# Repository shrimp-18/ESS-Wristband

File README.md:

# ESSync Wristband

A gesture-controlled referee wristband that automates match timing in Taekwondo. Using an accelerometer and microcontroller, it detects the referee’s calibrated start and stop gestures and wirelessly updates the central timer visible to everyone. This system removes manual jury control, ensuring accurate, fair, and transparent timekeeping.

---

## How it works

- Referee wants to stop the match.
- They make a swift hand movement used traditionally in Taekwondo.
- Players see this hand movement and stop.
- ESSync senses this swift hand movement and sends a signal to the central timer to stop.
- The central timer stops, and so do all the other sensors.
- Similar process repeats when the referee wants to restart the match.

<br>

---

## Why is ESSync Needed?

In Taekwondo matches, round timing is controlled by officials sitting at the jury table rather than by the referee overseeing the bout. This separation often leads to inconsistencies in the start and stop of the timer, whether due to human delay, miscommunication, or, in some cases, bias.
As a result, athletes can be unfairly advantaged or disadvantaged by inaccurate match durations, compromising the fairness and integrity of the competition.
There is a critical need for a referee-operated, automated, and transparent timing system that ensures real-time synchronisation and impartial timekeeping.

---

## So What's the solution?!

- A gesture-controlled wristband worn by referees to automate match timing.
- Uses an accelerometer and microcontroller to detect specific referee gestures.
- The downward "stop" motion of the hand instantly triggers the central arena timer wirelessly.
- Calibrated for each referee to prevent false detections and ensure precision.
- Removes jury dependency, ensuring fair, transparent, and real-time timekeeping.
- The timer part of Taekwondo matches isn’t automated yet and really needs a cheap and effective solution.
- Wristbands are easy to make and reliable.

---

## Components and their uses

| Component | Purpose |
|-----------|---------|
| ESP32-C3 DevKitM-1 | Main MCU, the "brain" of the wristband |
| MPU6050 | Detects referee hand gestures |
| 1.3" 240×240 SPI Display | Displays timer and status |
| MT3608 | Boost converter |
| TP4056 | LiPo battery charger |

---

## Top PCB

---

## Bottom PCB

The project is made with two PCBs. The upper PCB holds the display, while the bottom PCB contains the MCU and all other components. This approach keeps the wristband compact without making it too wide. In future revisions, I plan to make it even smaller. The Case closes shut using the magnets present on the bottom part of the case and the lid of the case. The PCBs are snug in the case. The bottom PCB is also mounted to the bottom case by simply fitting the PCB's holes over the protruding cylindrical parts on the inner base of the case.

---

## Fusion Files

https://a360.co/4gCFWl9

---

## How to Build

## 1. Manufacture the PCBs
Fabricate both the **Top PCB** and **Bottom PCB** using the KiCad Files provided.

---

## 2. Prepare the Components

Purchase all required components listed in the **Bill of Materials (BOM)**.

---

## 3. Solder the Bottom PCB

Assemble the Bottom PCB first.
Solder All components and connectors to the bottom PCB according to the KiCad files given, and attach their respective components.

Refer to the schematic for the correct connector orientation and pin mapping.

---

## 4. Assemble the Top PCB

1. Solder the female headers for the ESP32 connector(on the bottom side).
2. Solder the male headers for the SPI Screen(on the top side).
3. Connect the SPI Screen.

---

## 5. Join the Two PCBs

Carefully align the connector pins and stack the 2 PCBs.

---

## 6. Upload the Firmware

1. Connect the ESP32-C3 to your computer using a USB cable.
2. Open the firmware in the Arduino IDE.
3. Select **ESP32-C3 Dev Module** as the target board.
4. Choose the correct serial port.
5. Compile and upload the firmware.

## 7. Assemble the Enclosure

3D-print the enclosure using the CAD files.

Install the assembled electronics inside the case.
No screws are required to mount as the pcb is snug in the case.
Glue Magnets to the base and lid of the case so that it can remain closed.

---

## 8. Attach a Wrist Strap

The wrist strap is **not** 3D printed </3
It's a DIY thing you need to do with a leather sheet.
Please add a strap to the bottom case through the space given underneath (I will be updating this with a better option in the future).

---

## 9. Power On

If assembled correctly, ESSync should be working! YAY!

---
## How to Use

You'll need to calibrate your hand gestures with the watch so it can record those values and stop/start the timer the next time you use it.

## Bill of Materials

| S.No. | Reference | Value | Product | Notes | Qty | Cost | Link |
|------:|-----------|-------|---------|-------|----:|-----:|------|
| 1 | SPI_SCREEN1 | Conn_01x07 | Connector Pin Socket P2.54mm Vertical 1×7 | Top PCB (Display Connector) | 1 | $0.09 | https://robocraze.com/products/40x1-female-berg-strip |
| 2 | — | — | 1.3" 240×240 SPI Display | External Module | 1 | $9.50 | https://www.waveshare.com/1.3inch-lcd-module.htm |
| 3 | U3 | ESP32-C3-DevKitM-1 | ESP32-C3 DevKitM-1 | Bottom PCB | 1 | $10.11 | https://www.electropi.in/espressif-esp32-c3-devkitm-1-n4x-development-board |
| 4 | J1, J2 | Conn_01x15 | 1×15 Female Pin Socket | Bottom of Top PCB | 2 | $0.09 | https://robocraze.com/products/40x1-female-berg-strip |
| 5 | J7, J8, J9, J10 | Conn_01x01 | 1×01 Pin Header | MT3608 Connection | 4 | $0.06 | https://robocraze.com/products/40x1-pin-2-54mm-pitch-male-berg-strip |
| 6 | — | — | MT3608 Boost Module | External Module | 1 | $0.47 | https://www.flyrobo.in/mt3608-2a-dc-dc-boost-ultra-power-module |
| 7 | MPU6050 | Conn_01x08 | 1×08 Pin Header | MPU6050 Connector | 1 | $0.06 | https://robocraze.com/products/40x1-pin-2-54mm-pitch-male-berg-strip |
| 8 | — | — | MPU6050 Module | External Module | 1 | $1.63 | https://robocraze.com/products/mpu-6050-triple-axis-accelerometer-gyroscope-module |
| 9 | J5, J6, J11, J12 | Conn_01x01 | 1×01 Pin Header | TP4056 Connection | 4 | $0.06 | https://robocraze.com/products/40x1-pin-2-54mm-pitch-male-berg-strip |
| 10 | — | — | TP4056 Charging Module | External Module | 1 | $0.17 | https://quartzcomponents.com/products/tp4056-battery-charging-module |
| 11 | S1 | Tactile Button, 160gf | TS-1088-AR02016 | ESP ON Button | 1 | $0.06 | https://jlcpcb.com/partdetail/XUNPU-TS_1088AR02016/C720477 |
| 12 | SW1 | SW_Slide_DPDT | PCM12 Slide Switch | Power Switch | 1 | $1.20 | https://www.digikey.in/en/products/detail/c-k/PCM12SMTR/1640112 |
| 13 | Battery1 | Conn_01x02 | JST Battery Connector | Battery Connector | 1 | $0.05 | https://robu.in/product/b2b-xh-alfsn-jst-1x2p-2p-xh-tin-2-25%E2%84%8385%E2%84%83-3a-1-2-5mm-brass-direct-insert-pluginp2-5mm-wire-to-board-connector-rohs/ |
| 14 | — | — | 3.7V LiPo Battery | External Module | 1 | $1.69 | https://robocraze.com/products/450mah-3-7v-lipo-rechargeable-battery |
| 15 | C1 | 0.1µF | 0603 Capacitor | Decoupling Capacitor | 1 | $0.04 | https://robu.in/product/0603b104j500nt-fh-50v-100nf-x7r%C2%B15-0603-multilayer-ceramic-capacitors-mlcc-smd-smt-rohs/ |
| 16 | — | — | PCB Fabrication | Two Custom PCBs | 2 | $2.00 | https://cart.jlcpcb.com/quote |
| 17 | — | — | 3D Printed Case | External | 1 | $4.00 | https://zbotic.in/product/online-3d-printing-service |
| 18 | — | — | Leather Strap | External | 1 | $0.40 | https://www.desertcart.in/products/425174482-genuine-leather-strip-1-2-inch-wide-72-inches-long |
| 19 | — | — | Magnets | Externsl | 1 | $0.40 | https://www.prayogindia.in/product/neodymium-magnet-3mm-x-1mm-n35-super-strong-magnets/ |

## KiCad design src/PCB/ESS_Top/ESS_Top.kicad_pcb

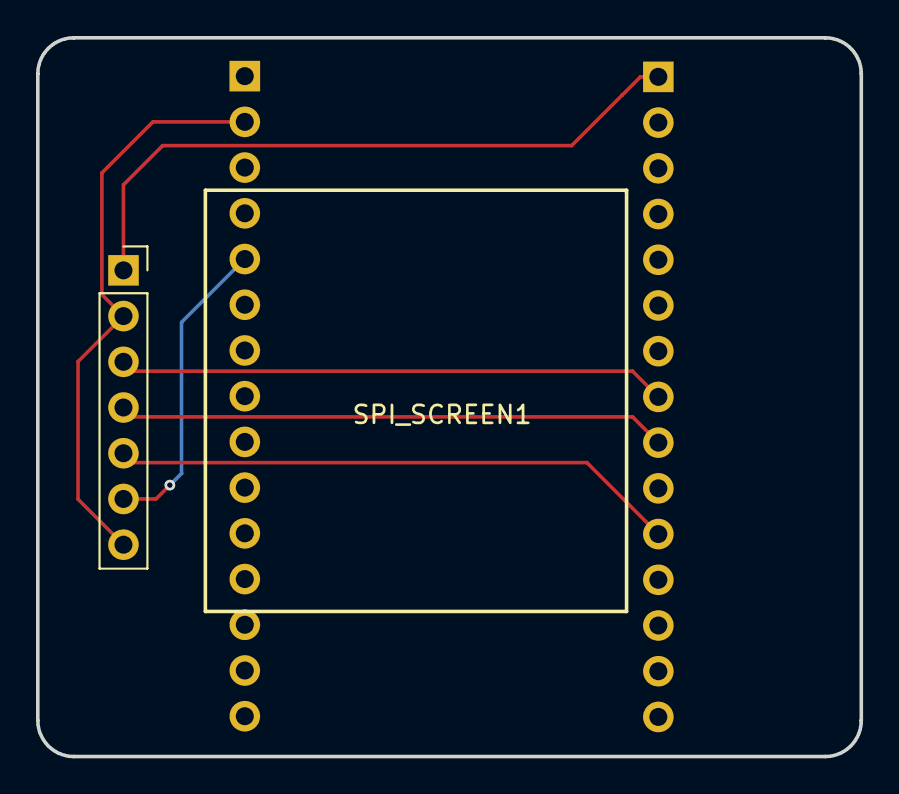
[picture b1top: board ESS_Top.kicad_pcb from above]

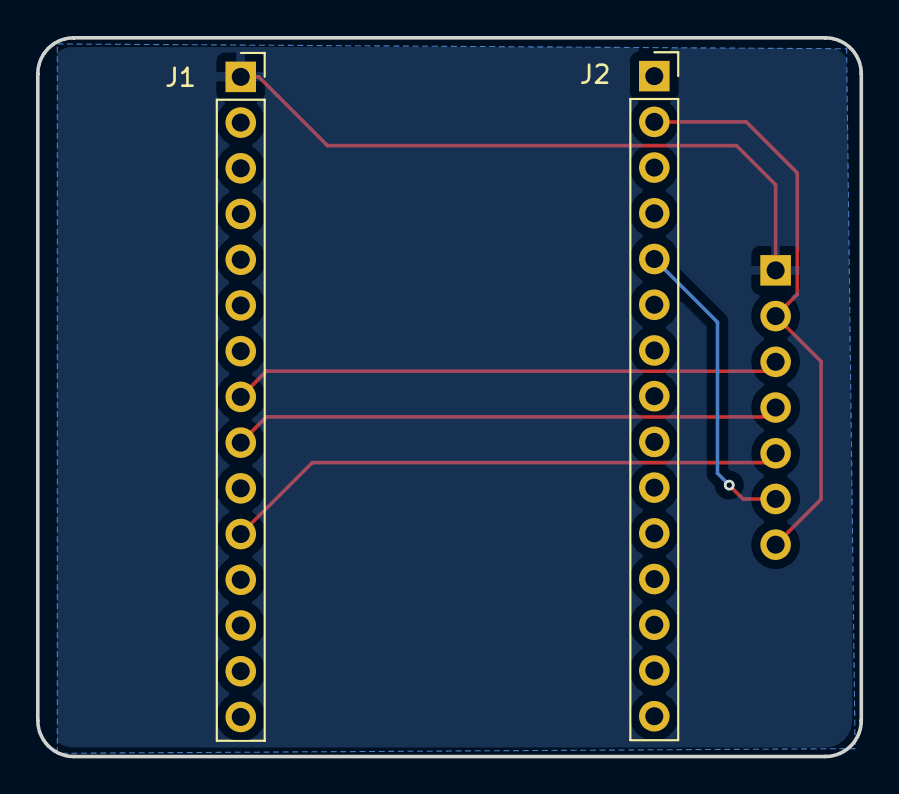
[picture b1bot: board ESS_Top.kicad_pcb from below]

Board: 2 copper layers, 45.7 x 39.9 mm, 3 parts (2 on the bottom side), 6 nets.

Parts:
J1, J2: Conn_01x15; PinSocket_1x15_P2.54mm_Vertical
SPI_SCREEN1: Conn_01x07; PinSocket_1x07_P2.54mm_Vertical

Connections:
+3.3V: J2.2 (3V3), SPI_SCREEN1.2, SPI_SCREEN1.7
/DC: J2.5 (GPIO3), SPI_SCREEN1.6
/RES: J1.11 (GPIO4), SPI_SCREEN1.5
/SCL_SPI: J1.8 (GPIO7), SPI_SCREEN1.3
/SDA_SPI: J1.9 (GPIO6), SPI_SCREEN1.4
GND: J1.1 (GND), SPI_SCREEN1.1

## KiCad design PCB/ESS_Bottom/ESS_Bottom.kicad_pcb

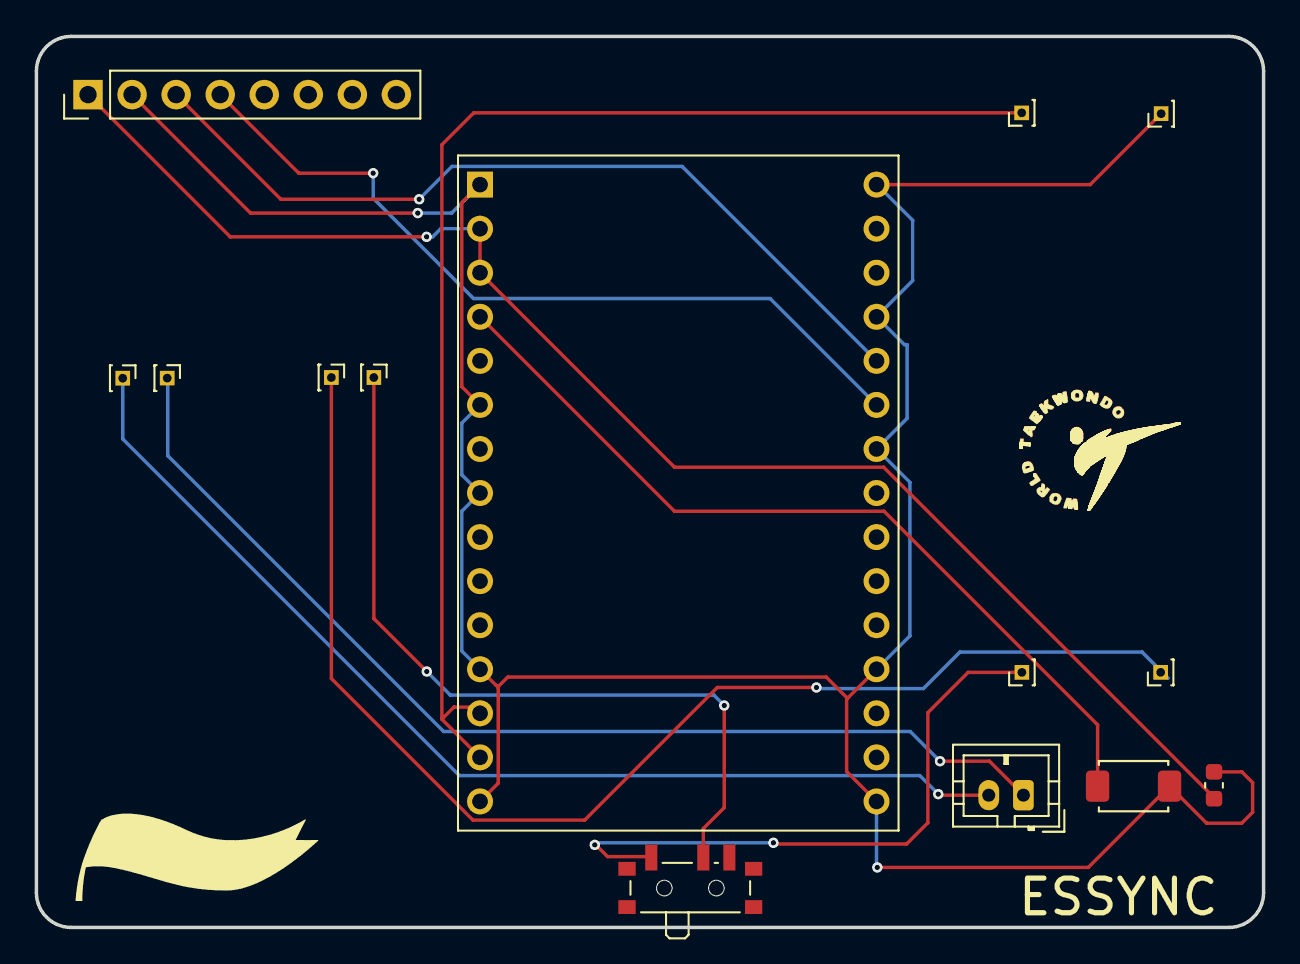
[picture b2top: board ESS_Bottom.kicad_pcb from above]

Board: 2 copper layers, 70.8 x 51.4 mm, 14 parts (0 on the bottom side), 11 nets.

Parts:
Battery1: Conn_01x02; JST_PH_B2B-PH-K_1x02_P2.00mm_Vertical
C1: 0.1uF; C_0603_1608Metric
J5, J6, J7, J8, J9, J10, J11, J12: Conn_01x01; PinHeader_1x01_P1.00mm_Vertical
MPU6050: Conn_01x08; PinHeader_1x08_P2.54mm_Vertical
S1: Tactile Button, 160gf; SW_TS-1088-AR02016
SW1: SW_Slide_DPDT; SW_SPDT_PCM12
U3: ESP32-C3-DevKitM-1

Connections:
+3.3V: C1.1, MPU6050.1, U3.2 (3V3), U3.3 (3V3)
+5V: J9.1, U3.13 (5V), U3.14 (5V)
/BAT+: Battery1.1, J11.1
/BAT-: Battery1.2, J12.1
/GPIO2: S1.1 (A), U3.4 (IO2)
/IN+: J7.1, SW1.1 (A)
/IN-: J6.1, J8.1
/OUT+: J5.1, SW1.2 (B)
/SCL: MPU6050.3, U3.26 (IO9)
/SDA: MPU6050.4, U3.25 (IO8)
GND: C1.2, J10.1, MPU6050.2, S1.2 (B), U3.1 (GND), U3.6 (GND), U3.8 (GND), U3.12 (GND), U3.15 (GND), U3.16 (GND), U3.19 (GND), U3.24 (GND), U3.27 (GND), U3.30 (GND)

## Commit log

2025-06-30 Entry1
2026-05-13 Added all ESSync files from KiCad
2026-05-13 3d models of components used in this project
2026-06-25 Added updated files of pcb
2026-06-25 added fusion links
2026-06-25 Organized files
2026-06-26 Added Zine
2026-06-27 added firmware files
2026-06-27 finished basic firmware and .bin files
2026-06-27 made kicad files cleaner?
2026-06-27 made firmware files cleaner?
2026-06-27 gitignore
2026-06-27 fixed gitignore
2026-06-27 added final cad file
2026-06-27 oooo hmmmm
2026-06-27 fab layer
2026-06-27 uploaded zine
2026-06-27 made src folder bcs alice told
2026-06-27 file names
2026-06-27 added ground fill
2026-06-27 deleted gitignore files
2026-06-27 smth
2026-06-27 ZINEZINEZINE MAGAZINE
2026-06-28 cadcad
2026-06-28 made holes in pcb for mounting
